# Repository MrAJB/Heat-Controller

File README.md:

# Heat Controller Project
Repo for the heat controller I am developing in my spare time. The goal is to develop some simple firmware and hardware to control a heating element. 

Feel free to look around and re-use (pieces of) this project!

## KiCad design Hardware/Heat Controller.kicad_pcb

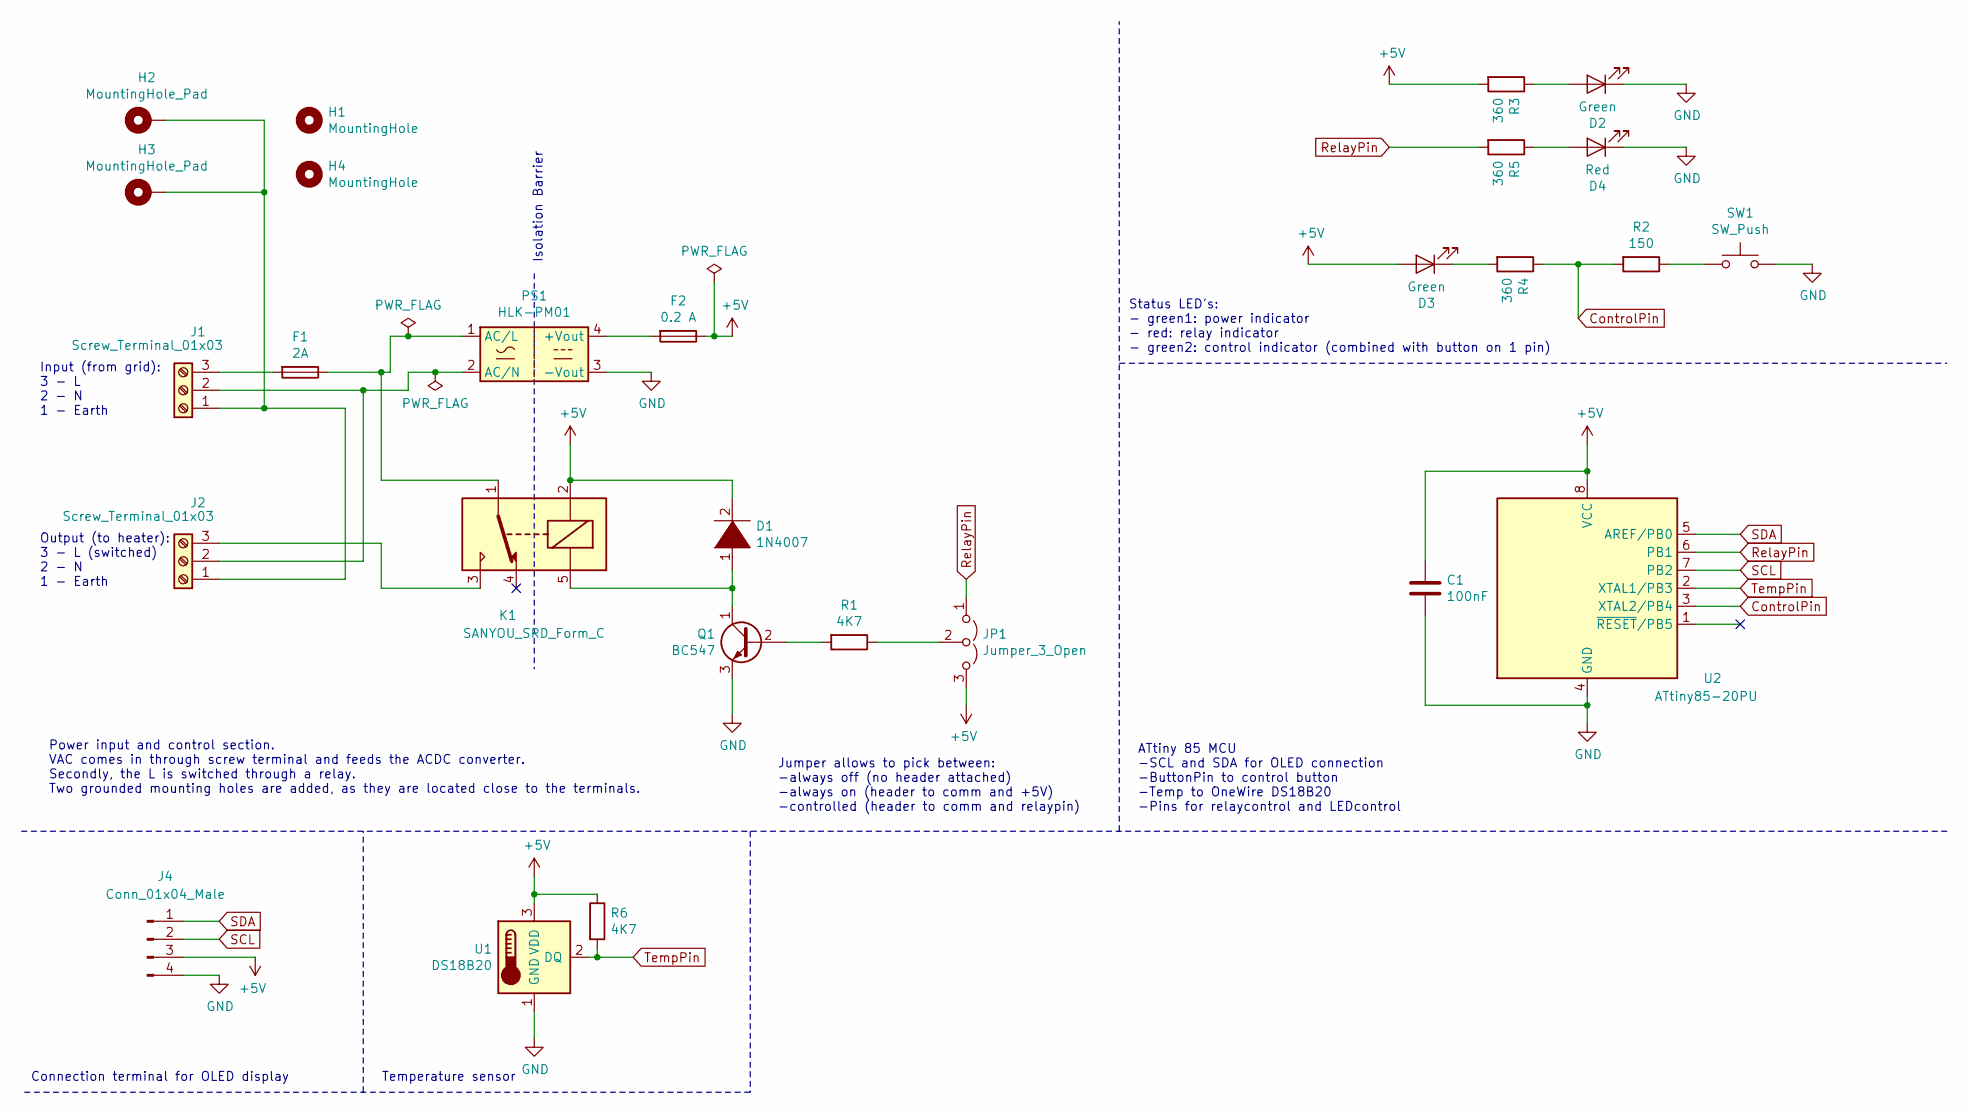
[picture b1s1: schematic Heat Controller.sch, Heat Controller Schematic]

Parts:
C1: 100nF; CP_Radial_D4.0mm_P1.50mm
D1: 1N4007; D_DO-41_SOD81_P10.16mm_Horizontal
D2, D3: Green; LED_D3.0mm
D4: Red; LED_D3.0mm
F1: 2A; Fuse_Holder_04x20
F2: 0.2 A; Fuse_Holder_04x20
H1: MountingHole; MountingHole_3.2mm_M3_ISO7380
H2, H3: MountingHole_Pad; MountingHole_3.2mm_M3_ISO7380_Pad
H4: MountingHole; MountingHole_4.5mm
J1, J2: Screw_Terminal_01x03; ScrewTerminal_01x03_HeavyDuty
J4: Conn_01x04_Male; PinHeader_1x04_P2.54mm_Vertical
JP1: Jumper_3_Open; PinHeader_1x03_P2.54mm_Vertical
K1: SANYOU_SRD_Form_C; Relay_SPDT_SANYOU_SRD_Series_Form_C
PS1: HLK-PM01; Converter_ACDC_HiLink_HLK-PMxx
Q1: BC547; TO-92_Inline
R1, R6: 4K7; R_Axial_DIN0207_L6.3mm_D2.5mm_P7.62mm_Horizontal
R2: 150; R_Axial_DIN0207_L6.3mm_D2.5mm_P7.62mm_Horizontal
R3, R4, R5: 360; R_Axial_DIN0207_L6.3mm_D2.5mm_P7.62mm_Horizontal
SW1: SW_Push; SW_Push_1P1T_NO_6x6mm_H9.5mm
U1: DS18B20; TO-92_Inline
U2: ATtiny85-20PU; DIP-8_W7.62mm

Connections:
+5V: C1.1, D1.2 (A), D3.2 (A), F2.1, J4.3, JP1.3 (B), K1.2, R3.2, R6.1, U1.3 (VDD), U2.8 (VCC)
ControlPin: R2.2, R4.1, U2.3 (XTAL2/PB4)
GND: C1.2, D2.1 (K), D4.1 (K), J4.4, PS1.3 (-Vout), Q1.3 (E), SW1.2, U1.1 (GND), U2.4 (GND)
unnamed: D1.1 (K), K1.5, Q1.1 (C)
unnamed: D2.2 (A), R3.1
unnamed: D3.1 (K), R4.2
unnamed: D4.2 (A), R5.1
unnamed: F1.1, K1.1, PS1.1 (AC/L)
unnamed: F1.2, J1.3
unnamed: F2.2, PS1.4 (+Vout)
unnamed: H2.1, H3.1, J1.1, J2.1
unnamed: J1.2, J2.2, PS1.2 (AC/N)
unnamed: J2.3, K1.3
unnamed: JP1.2 (C), R1.1
unnamed: Q1.2 (B), R1.2
unnamed: R2.1, SW1.1
RelayPin: JP1.1 (A), R5.2, U2.6 (PB1)
SCL: J4.2, U2.7 (PB2)
SDA: J4.1, U2.5 (AREF/PB0)
TempPin: R6.2, U1.2 (DQ), U2.2 (XTAL1/PB3)

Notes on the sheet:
Input (from grid): 3 - L 2 - N 1 - Earth
Output (to heater): 3 - L (switched) 2 - N 1 - Earth
Isolation Barrier
Power input and control section. VAC comes in through screw terminal and feeds the ACDC converter. Secondly, the L is switched through a relay. Two grounded mounting holes are added, as they are located close to the terminals.
Jumper allows to pick between: -always off (no header attached) -always on (header to comm and +5V) -controlled (header to comm and relaypin)
Connection terminal for OLED display
Temperature sensor
Status LED's: - green1: power indicator - red: relay indicator - green2: control indicator (combined with button on 1 pin)
ATtiny 85 MCU -SCL and SDA for OLED connection -ButtonPin to control button -Temp to OneWire DS18B20 -Pins for relaycontrol and LEDcontrol

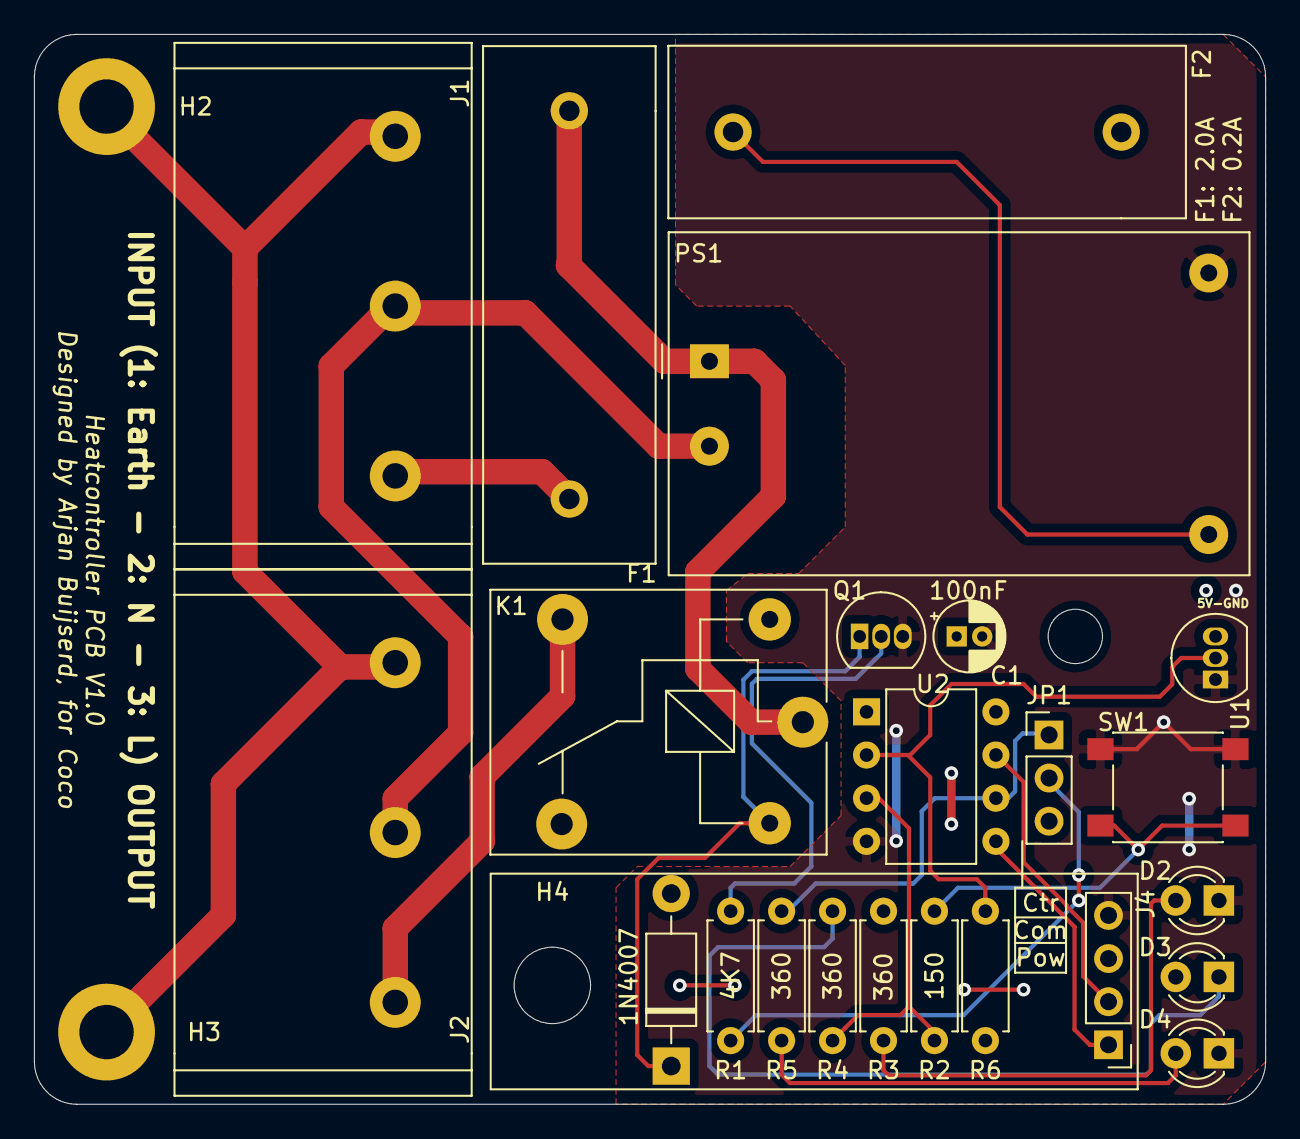
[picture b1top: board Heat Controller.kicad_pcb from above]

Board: 2 copper layers, 72.5 x 63.0 mm, 27 parts (0 on the bottom side), 20 nets.

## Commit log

2020-10-11 Added schematic files from local folder.
2020-10-11 Added documentation and firmware
2020-10-11 ATtiny 85 datasheet added
2020-10-11 Updated PCB according to schematic change.
    Added 4K7 resistor for one-wire signal line. Updated connections to ATtiny85 to work with I2C OLED display. To be rerouted.
2020-10-11 Remplaced normal terminal for jumper
2020-10-11 Minor changes
2020-10-21 Moved Arduino file in main folder
2020-10-23 Defined software structure, added OLED support
2020-10-23 Implemented code for temperature readings
2020-10-24 Added temp support, custom messages display
2020-10-25 Tested temp sensor. Ran into memory issues.
2020-10-26 Code brainstorm added
2020-10-26 Modded main according to pseudo_code
2020-10-26 Found interrupt example
2020-10-26 Revisited setup loop
2020-10-26 Temperature reading and checking functionality
2020-10-26 Finished LED helper functions
2020-10-26 Implemented LED blinks for debugging
2020-10-26 Modified main to not move PB5, updated pseudo
2020-10-26 Removed debugging statements
2020-10-28 Using char[] over String to save memory
2020-10-28 Minor updates
2020-10-28 No longer using interrupts
2020-10-28 Modified start-up sequence
2020-10-28 Typo
2020-10-28 Invert control LED, test function to read switch
    Used 360 ohm R for LED, 150 ohm R for button.
2020-10-28 Made function neat
2020-10-28 Test vias for ADCD converter
2020-11-02 Fixed multiple TODOs, implemented main loop
2020-11-02 Prepared PCB for ordering
2020-11-02 Added STEP file for case design
2020-11-12 Display temperatures on display
2020-11-12 Display to Dutch, implemented rest functionality
2020-11-23 Minor progression
2020-11-28 Added temp solidworks files
2020-11-28 Finished all parts for first print
2020-11-28 Added runtime display
    Still contains bug, integers are not displayed
2020-11-28 Set correct temp values and fixed display issue
2020-11-28 Deleted all unneeded README files
2020-11-28 Update runtime straight after reset
2020-11-28 Relay transistor datasheet
2020-11-28 Resolved first issues after printing bottom
2020-12-30 Resolved final issues
2020-12-30 Generated STLs for printing
2020-12-30 Minor changes/fixes
2020-12-31 Updated date in top part
2021-01-01 Iterated display slot dimensions
2021-01-02 Updated button
    Modified hole position and increased length a bit.
2021-01-02 Modded blinking sequences
